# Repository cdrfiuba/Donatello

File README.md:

# Donatello

Seguidor de línea para Liga Nacional de Robótica.

Simple, lento pero confiable.

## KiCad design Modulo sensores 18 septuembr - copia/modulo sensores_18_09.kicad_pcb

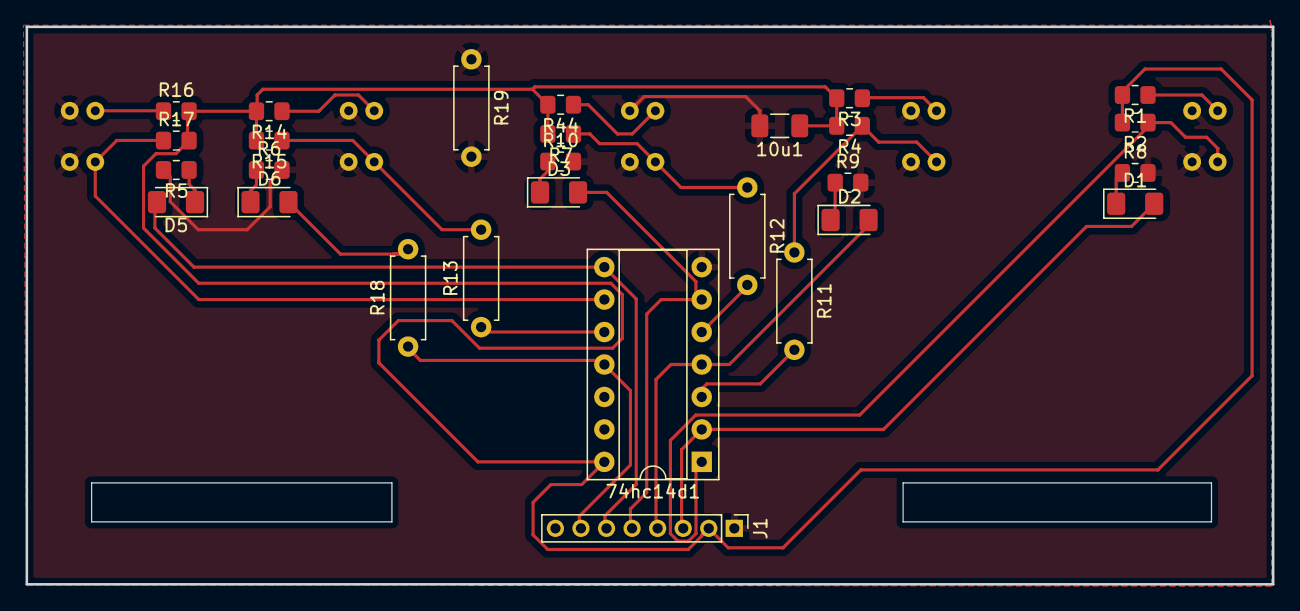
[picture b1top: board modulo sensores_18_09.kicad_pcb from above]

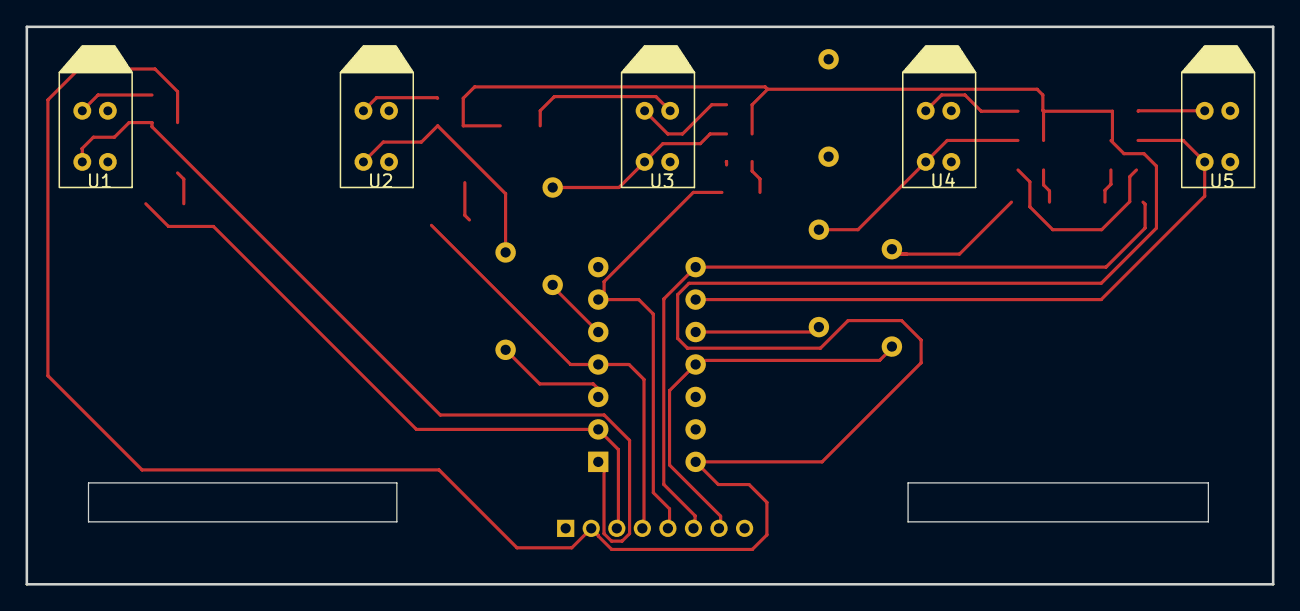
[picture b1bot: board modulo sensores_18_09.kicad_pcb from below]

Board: 2 copper layers, 97.5 x 43.6 mm, 33 parts (5 on the bottom side), 26 nets.

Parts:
10u1: CAP; C_1206_3216Metric_Pad1.33x1.80mm_HandSolder
74hc14d1: A_14-LC-TT; DIP-14_W7.62mm_Socket
D1, D2, D3, D5, D6: LED; LED_1206_3216Metric_Pad1.42x1.75mm_HandSolder
J1: Conn_01x08_Male; PinHeader_1x08_P2.00mm_Vertical
R1, R3, R14, R16, R44: 221; R_0805_2012Metric_Pad1.20x1.40mm_HandSolder
R2, R4, R7, R15, R17: 103; R_0805_2012Metric_Pad1.20x1.40mm_HandSolder
R5, R6, R8, R9, R10: 102; R_0805_2012Metric_Pad1.20x1.40mm_HandSolder
R11, R12, R13, R18, R19: 0; R_Axial_DIN0207_L6.3mm_D2.5mm_P7.62mm_Horizontal
U1, U2, U3, U4, U5: TCMT4106; tcrt5000

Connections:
/pin8: D6.2 (A), J1.7, R18.2
GND: 10u1.2, 74hc14d1.7, J1.1, R5.2, R6.2, R8.2, R9.2, R10.2, R19.1, R19.2, U1.2, U1.15, U2.2, U2.15, U3.2, U3.15, U4.2, U4.15, U5.2, U5.15
unnamed: 74hc14d1.1, R2.1, U1.16
unnamed: 74hc14d1.2, D1.2 (A), J1.3
unnamed: 74hc14d1.3, R11.2
unnamed: 74hc14d1.4, D2.2 (A), J1.4
unnamed: 74hc14d1.5, R12.2
unnamed: 74hc14d1.6, D3.2 (A), J1.5
unnamed: 74hc14d1.8, D5.2 (A), J1.6
unnamed: 74hc14d1.10, R13.1
unnamed: 74hc14d1.11, R18.1
unnamed: D1.1 (K), R8.1
unnamed: D2.1 (K), R9.1
unnamed: D3.1 (K), R10.1
unnamed: D5.1 (K), R5.1
unnamed: D6.1 (K), R6.1
unnamed: R1.1, U1.1
unnamed: R3.1, U2.1
unnamed: R4.1, R11.1, U2.16
unnamed: R7.1, R12.1, U3.16
unnamed: R14.1, U4.1
unnamed: R13.2, R15.1, U4.16
unnamed: R16.1, U5.1
unnamed: 74hc14d1.9, R17.1, U5.16
unnamed: R44.1, U3.1
VCC: 10u1.1, 74hc14d1.14, J1.2, R1.2, R2.2, R3.2, R4.2, R7.2, R14.2, R15.2, R16.2, R17.2, R44.2

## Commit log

2023-06-02 modify .gitignore
2023-06-02 Everything else
2023-06-09 leonel
2023-06-09 Archivos iniciales del seguidor
2023-06-09 mensaje
2023-06-09 cambios
2023-06-09 Arduino.h
2023-06-10 ahora compila :)
2023-06-10 lo que sea
2023-06-13 Control P entre otras cosas
2023-06-30 Update codigo_fsm.cpp
    *
2023-06-30 blah blah lfs
2023-07-15 freecad
2023-08-01 Add board files
2023-08-01 Add CAD files.
2023-08-27 Update the PCB so it matches the sizes of the boards we have
2023-08-30 placa 5 sensores
2023-09-01 New pcb design Add .gitignore
2023-09-08 codigo que funciona
2023-09-08 funciona
2023-09-16 placa
2023-09-21 placa ruteada
2023-09-22 sensores
2023-10-02 maquina de estados
2023-10-05 retoque codigo pid y funciona la mascara de sensores
2023-10-07 Codigo funcional pre-competencia
2023-10-07 Codigos Liga nacional Hurlingham BOKEEEEEE
